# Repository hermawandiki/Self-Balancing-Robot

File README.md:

# Self-Balancing-Robot

The self-balancing robot is equipped with a remote on a mobile phone that can be used to control the movement of the robot and the gripper.

This self-balancing robot was developed in the robotics project course in Mechatronic Engineering - EEPIS

Course lecturer : Eko Henfri Binugroho, S.ST., M. Eng.

Mechatronics Engineering Study Program

Electronic Engineering Polytechnic Institute of Surabaya (EEPIS)

#

Robot self-balancing ini dilengkapi dengan remote pada ponsel yang dapat digunakan untuk mengontrol pergerakan robot dan gripper.

Robot self-balancing ini dikembangkan dalam mata kuliah proyek robotika di Teknik Mekatronika - PENS

Dosen Mata Kuliah : Eko Henfri Binugroho, S.ST., M. Eng.

Program Studi Teknik Mekatronika

Politeknik Elektronika Negeri Surabaya (PENS)

#

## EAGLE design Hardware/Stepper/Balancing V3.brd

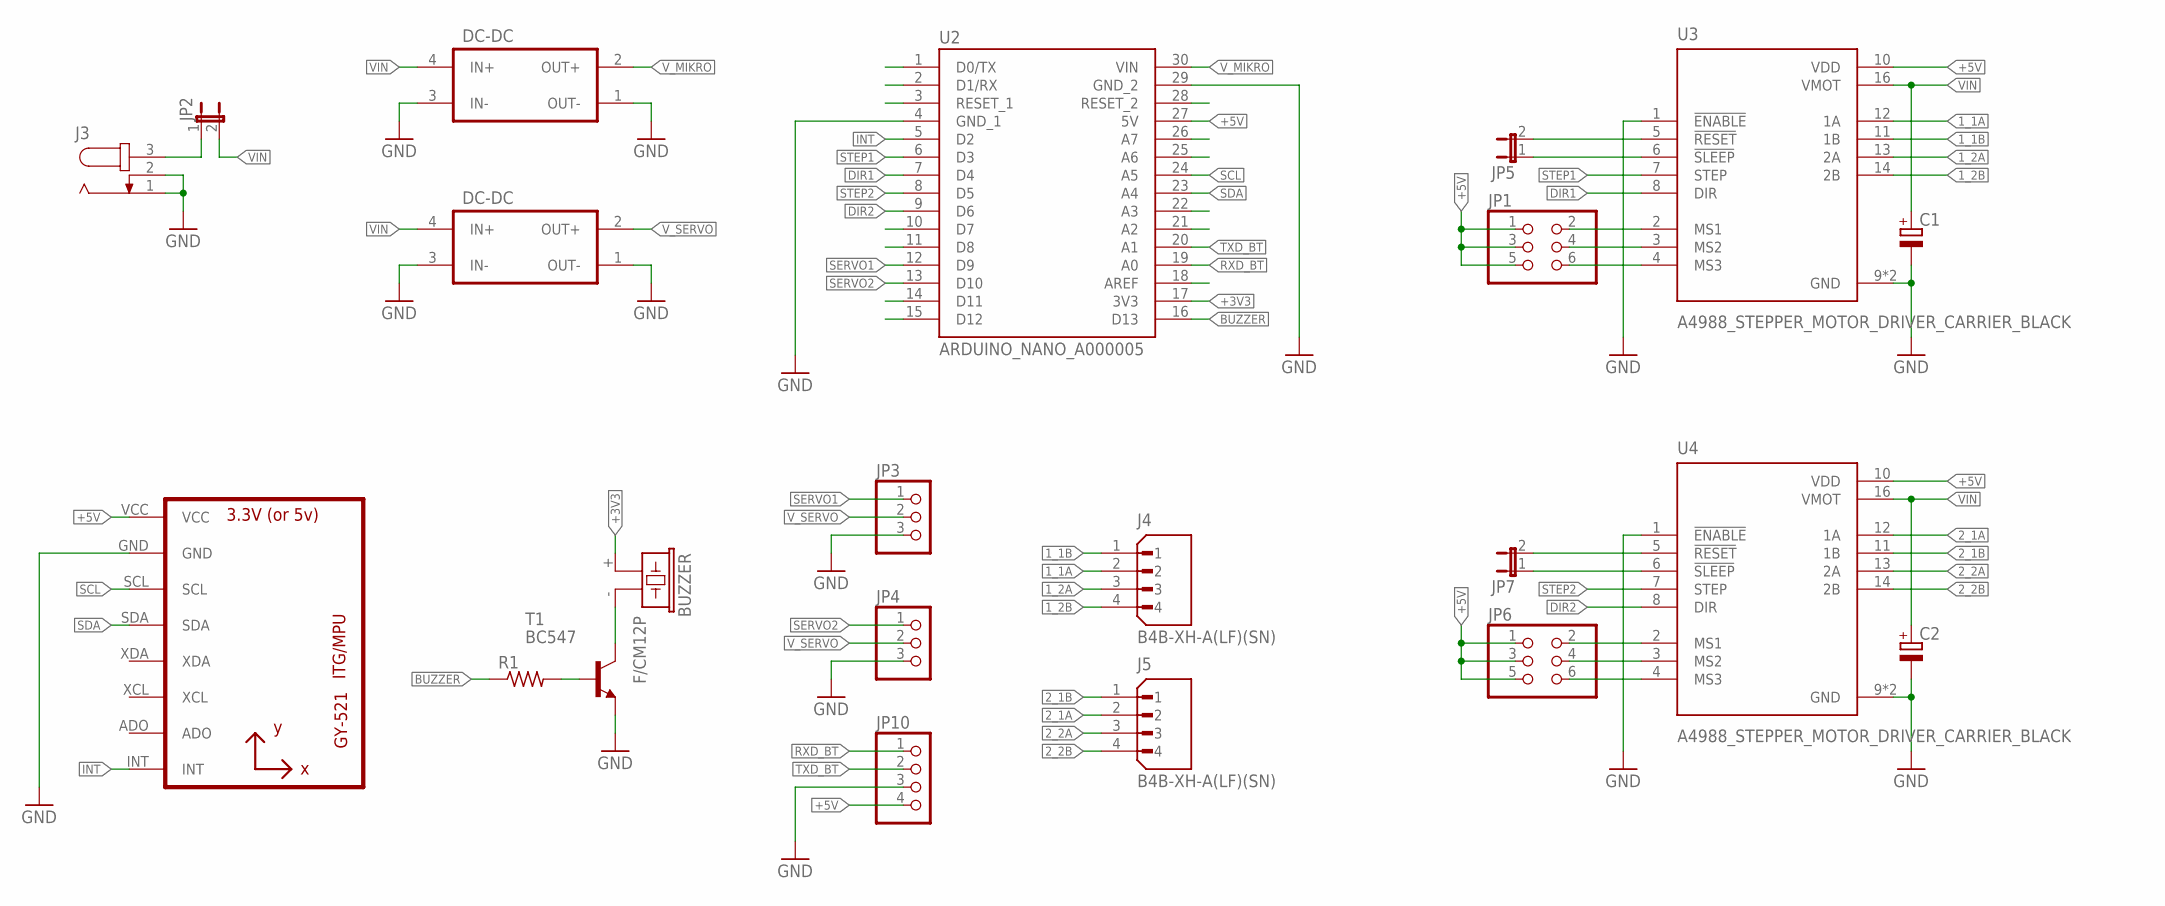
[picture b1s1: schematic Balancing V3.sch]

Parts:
BUZZER: F/CM12P
C1, C2: CPOL-EUE2.5-6; E2,5-6
J3: JACK-PLUG1; SPC4078
J4, J5: B4B-XH-A(LF)(SN); JST_B4B-XH-A(LF)(SN)
JP1, JP6: PINHD-2X3; 2X03
JP2, JP5, JP7: JP1E; JP1
JP3, JP4: PINHD-1X3; 1X03
JP10: PINHD-1X4; 1X04
R1: R-US_0204/7; 0204/7
T1: BC547; TO92
U1: GY-521MPU6050; GY-521
U2: ARDUINO_NANO_A000005; MODULE_ARDUINO_NANO_A000005
U3, U4: A4988_STEPPER_MOTOR_DRIVER_CARRIER_BLACK; MODULE_A4988_STEPPER_MOTOR_DRIVER_CARRIER_BLACK
U$1, U$2: DC-DC_CONV

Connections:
1_1A: J4.2, U3.12 (1A)
1_1B: J4.1, U3.11 (1B)
1_2A: J4.3, U3.13 (2A)
1_2B: J4.4, U3.14 (2B)
2_1A: J5.2, U4.12 (1A)
2_1B: J5.1, U4.11 (1B)
2_2A: J5.3, U4.13 (2A)
2_2B: J5.4, U4.14 (2B)
+3V3: BUZZER.+ (1), U2.17 (3V3)
+5V: JP1.1, JP1.3, JP1.5, JP6.1, JP6.3, JP6.5, JP10.4, U1.VCC, U2.27 (5V), U3.10 (VDD), U4.10 (VDD)
BUZZER: R1.1, U2.16 (D13)
DIR1: U2.7 (D4), U3.8 (DIR)
DIR2: U2.9 (D6), U4.8 (DIR)
GND: C1.-, C2.-, J3.1, J3.2, JP3.3, JP4.3, JP10.3, T1.1 (E), U1.GND, U2.4 (GND_1), U2.29 (GND_2), U3.1 (!ENABLE), U3.9 (GND), U3.15 (GND), U4.1 (!ENABLE), U4.9 (GND), U4.15 (GND), U$1.1 (OUT-), U$1.3 (IN-), U$2.1 (OUT-), U$2.3 (IN-)
INT: U1.INT, U2.5 (D2)
unnamed: R1.2, T1.2 (B)
unnamed: BUZZER.- (2), T1.3 (C)
unnamed: JP1.2, U3.2 (MS1)
unnamed: J3.3, JP2.1
unnamed: JP1.4, U3.3 (MS2)
unnamed: JP1.6, U3.4 (MS3)
unnamed: JP7.2, U4.5 (!RESET)
unnamed: JP7.1, U4.6 (!SLEEP)
unnamed: JP6.2, U4.2 (MS1)
unnamed: JP6.4, U4.3 (MS2)
unnamed: JP6.6, U4.4 (MS3)
unnamed: JP5.2, U3.5 (!RESET)
unnamed: JP5.1, U3.6 (!SLEEP)
RXD_BT: JP10.1, U2.19 (A0)
SCL: U1.SCL, U2.24 (A5)
SDA: U1.SDA, U2.23 (A4)
SERVO1: JP3.1, U2.12 (D9)
SERVO2: JP4.1, U2.13 (D10)
STEP1: U2.6 (D3), U3.7 (STEP)
STEP2: U2.8 (D5), U4.7 (STEP)
TXD_BT: JP10.2, U2.20 (A1)
VIN: C1.+, C2.+, JP2.2, U3.16 (VMOT), U4.16 (VMOT), U$1.4 (IN+), U$2.4 (IN+)
V_MIKRO: U2.30 (VIN), U$1.2 (OUT+)
V_SERVO: JP3.2, JP4.2, U$2.2 (OUT+)

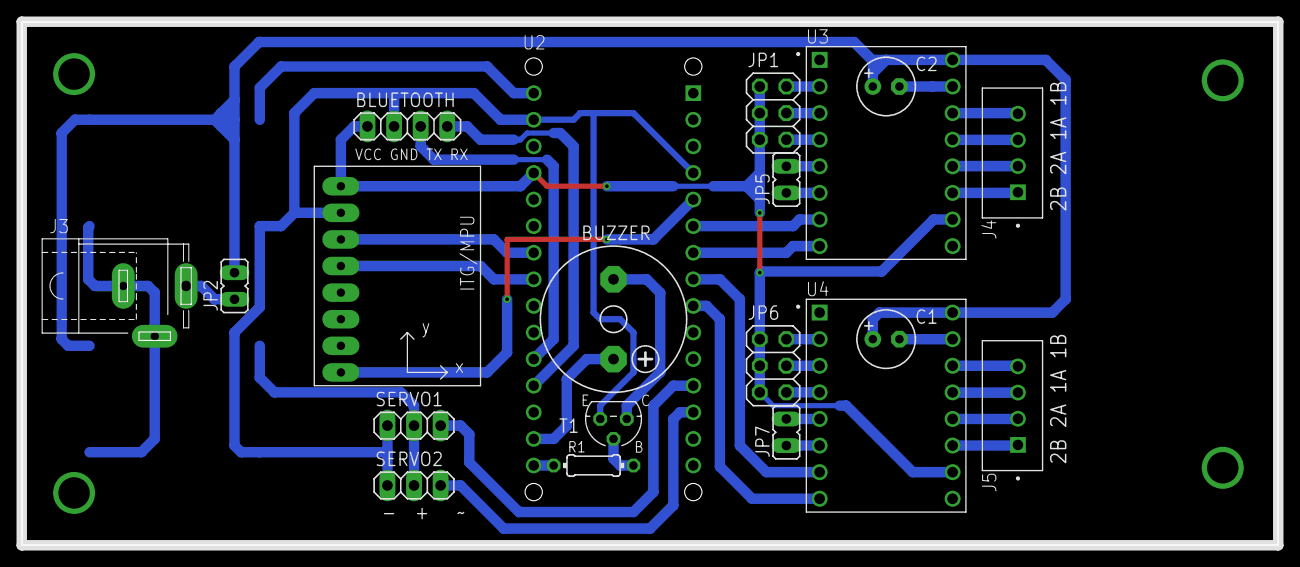
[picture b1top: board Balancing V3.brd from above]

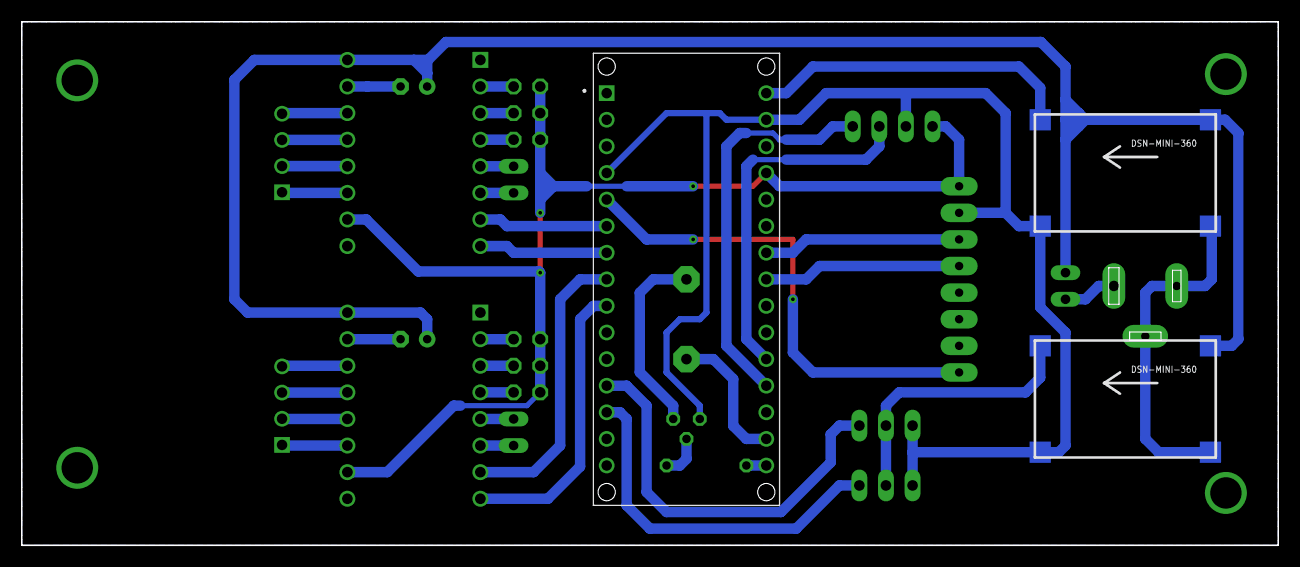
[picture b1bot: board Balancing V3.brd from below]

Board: 2 copper layers, 120.0 x 50.0 mm, 22 parts (3 on the bottom side), 39 nets.

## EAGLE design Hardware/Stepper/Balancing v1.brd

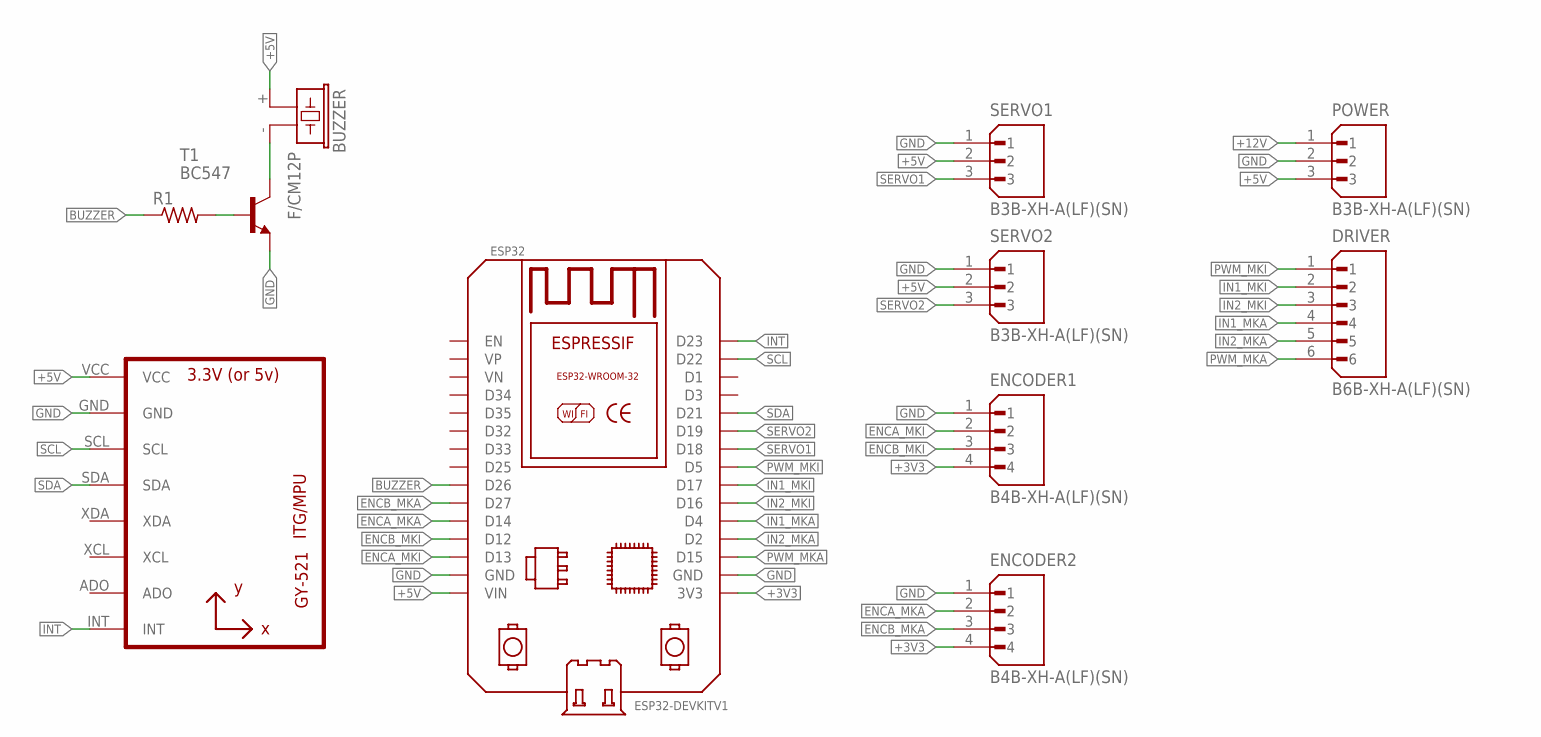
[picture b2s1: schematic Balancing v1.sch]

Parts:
BUZZER: F/CM12P
DRIVER: B6B-XH-A(LF)(SN); JST_B6B-XH-A(LF)(SN)
ENCODER1, ENCODER2: B4B-XH-A(LF)(SN); JST_B4B-XH-A(LF)(SN)
ESP32: ESP32DEVKITV1; ESP32-DEVKITV1
POWER: B3B-XH-A(LF)(SN); JST_B3B-XH-A(LF)(SN)
R1: R-US_0204/7; 0204/7
SERVO1, SERVO2: B3B-XH-A(LF)(SN); JST_B3B-XH-A(LF)(SN)
T1: BC547; TO92
U1: GY-521MPU6050; GY-521

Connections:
+3V3: ENCODER1.4, ENCODER2.4, ESP32.3V3
+5V: BUZZER.+ (1), ESP32.VIN, POWER.3, SERVO1.2, SERVO2.2, U1.VCC
+12V: POWER.1
BUZZER: ESP32.D26, R1.1
ENCA_MKA: ENCODER2.2, ESP32.D14
ENCA_MKI: ENCODER1.2, ESP32.D13
ENCB_MKA: ENCODER2.3, ESP32.D27
ENCB_MKI: ENCODER1.3, ESP32.D12
GND: ENCODER1.1, ENCODER2.1, ESP32.GND, ESP32.GND@1 (GND), POWER.2, SERVO1.1, SERVO2.1, T1.1 (E), U1.GND
IN1_MKA: DRIVER.4, ESP32.D4
IN1_MKI: DRIVER.2, ESP32.D17
IN2_MKA: DRIVER.5, ESP32.D2
IN2_MKI: DRIVER.3, ESP32.D16
INT: ESP32.D23, U1.INT
unnamed: R1.2, T1.2 (B)
unnamed: BUZZER.- (2), T1.3 (C)
PWM_MKA: DRIVER.6, ESP32.D15
PWM_MKI: DRIVER.1, ESP32.D5
SCL: ESP32.D22, U1.SCL
SDA: ESP32.D21, U1.SDA
SERVO1: ESP32.D18, SERVO1.3
SERVO2: ESP32.D19, SERVO2.3

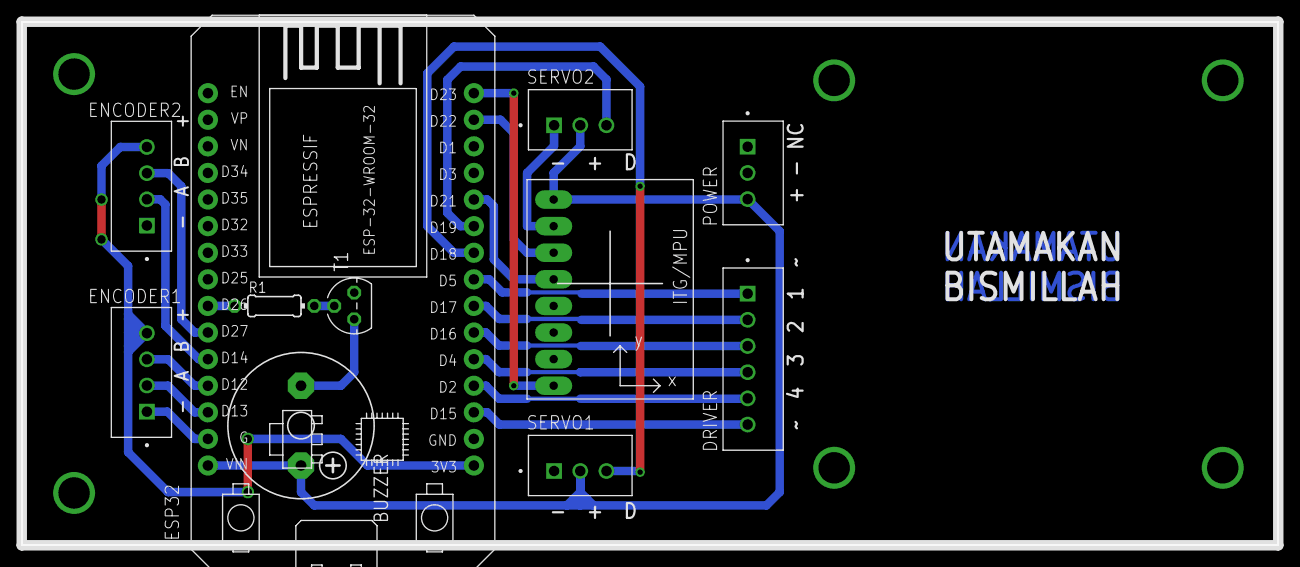
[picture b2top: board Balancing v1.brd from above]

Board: 2 copper layers, 120.0 x 50.0 mm, 11 parts (0 on the bottom side), 21 nets.

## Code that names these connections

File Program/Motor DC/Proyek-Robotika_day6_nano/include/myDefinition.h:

#ifndef __MYDEFINITION_H__
#define __MYDEFINITION_H__

#include <Arduino.h>

#define DEBUG 0

#if DEBUG == 0
#define debug(x) monitor.print(x);
#define debugln(x) monitor.println(x);
#else
#define debug(x)
#define debugln(x)
#endif

// PID
#define KpPitch 17.0  // 10 // 16 // 16 // 16
#define KdPitch 0.8  // 0.01 // 0.7 // 0.9 / 0.7
#define KiPitch 194.5  // 30 // 77 // 95 // 153

#define KpYaw 14.0
#define KdYaw 0.3
#define KiYaw 20.02

#define KpPos 0.0
#define KdPos 0.0
#define KiPos 0.0

// Motor Driver
#define PWM_MKI 9
#define IN1_MKI A3
#define IN2_MKI A2
#define IN1_MKA A1
#define IN2_MKA A0
#define PWM_MKA 10

// Serial Communication
#define RX_PIN_BT 0
#define TX_PIN_BT 1
#define RX_MONITOR 11
#define TX_MONITOR 12

// MPU6050
#define INT_PIN 4

// Encoder
#define ENCA_MKI 2
#define ENCB_MKI 7
#define ENCA_MKA 3
#define ENCB_MKA 8

// Servo
#define SERVO1_PIN 5
#define SERVO2_PIN 6

// Buzzer
#define BUZZER_PIN 13
#define BuzzOn digitalWrite(BUZZER_PIN, HIGH)
#define BuzzOff digitalWrite(BUZZER_PIN, LOW)
#define BuzzTit(y) {for(uint8_t ii=0; ii<y; ii++){BuzzOn; delay(70); BuzzOff; delay(70);}}

// Global Variable
extern uint8_t lastStateA1, lastStateB1, lastStateA2, lastStateB2;
extern volatile int encoderM1, encoderM2;
extern double spPitch, spYaw;

// Function Prototype
extern void configIO();
extern void motor(int16_t pwm1, int16_t pwm2);
extern void handleEncMki();
extern void handleEncMka();

#endif

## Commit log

2024-10-24 move from local to github
2024-11-21 from local
2024-12-01 update ok
2024-12-03 update siap race
2024-12-04 update, race day 1
2024-12-05 final update, race day 2
